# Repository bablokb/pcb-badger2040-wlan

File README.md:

pcb-badger2040-wlan
===================

A small pcb that allows to add an ESP-01S and/or PCF8523-RTC-breakout
to the back of a Pimoroni Badger2040 (or Tufty2040):

  - Badger2040 with SMD-pins:  

  - PCB added:  

  - ESP-01S connected:  

  - Additionally with RTC (PCF8523):  

Note that the images show an old Rev 3 version of the PCB.

Design-Files
------------

KiCAD source files are in `badger-2040-wlan.kicad`. Production files
for JLCPCB are in directory `production`. Since the pcb does not
need any SMD-components (in Rev 4), these pcb are really easy
to order (just upload the zip) and cheap (I got five for less
than 7 Euro).

Hack to wakeup the Badger2040 using the RTC
-------------------------------------------

If you don't use the ESP-01S, you can connect the
RTC-alarm pin to the INT-pin by closing the jumper on the
back. Note that wakeup will only work with battery if you
constantly hold one of the buttons pressed
(see <https://github.com/bablokb/badger2040-button-clamp>).

Also, wakup is currently not implemented in MicroPython.

License
-------

[![CC BY-SA 4.0][cc-by-sa-shield]][cc-by-sa]

This work is licensed under a
[Creative Commons Attribution-ShareAlike 4.0 International
License][cc-by-sa].

[![CC BY-SA 4.0][cc-by-sa-image]][cc-by-sa]

[cc-by-sa]: http://creativecommons.org/licenses/by-sa/4.0/
[cc-by-sa-image]: https://licensebuttons.net/l/by-sa/4.0/88x31.png
[cc-by-sa-shield]:
https://img.shields.io/badge/License-CC%20BY--SA%204.0-lightgrey.svg

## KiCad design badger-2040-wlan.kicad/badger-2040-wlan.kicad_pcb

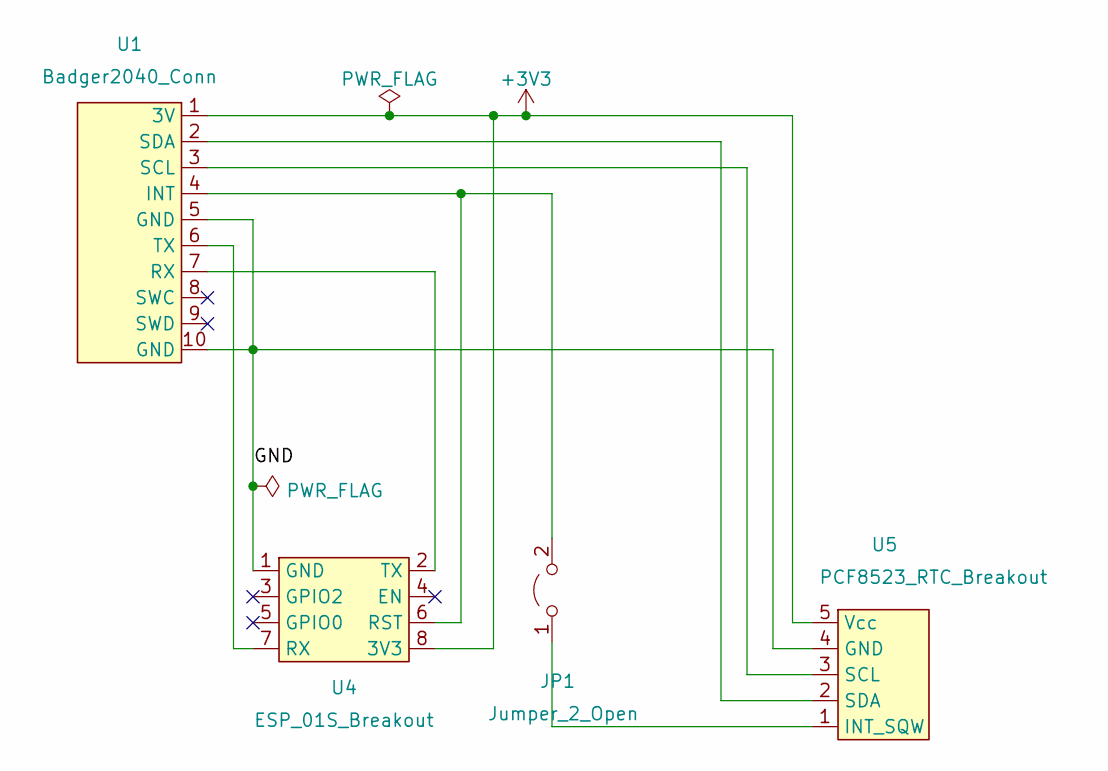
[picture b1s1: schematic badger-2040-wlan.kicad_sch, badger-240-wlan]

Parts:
JP1: Jumper_2_Open; SolderJumper-2_P1.3mm_Open_Pad1.0x1.5mm
U1: Badger2040_Conn; PinSocket_1x10_P2.54mm_Horizontal_Back
U4: ESP_01S_Breakout
U5: PCF8523_RTC_Breakout; PCF8523_Breakout

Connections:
+3V3: U1.1 (3V), U4.8 (3V3), U5.5 (Vcc)
/GND: U1.5 (GND), U1.10 (GND), U4.1 (GND), U5.4 (GND)
unnamed: JP1.1 (A), U5.1 (INT_SQW)
unnamed: JP1.2 (B), U1.4 (INT), U4.6 (RST)
unnamed: U1.2 (SDA), U5.2 (SDA)
unnamed: U1.3 (SCL), U5.3 (SCL)
unnamed: U1.6 (TX), U4.7 (RX)
unnamed: U1.7 (RX), U4.2 (TX)

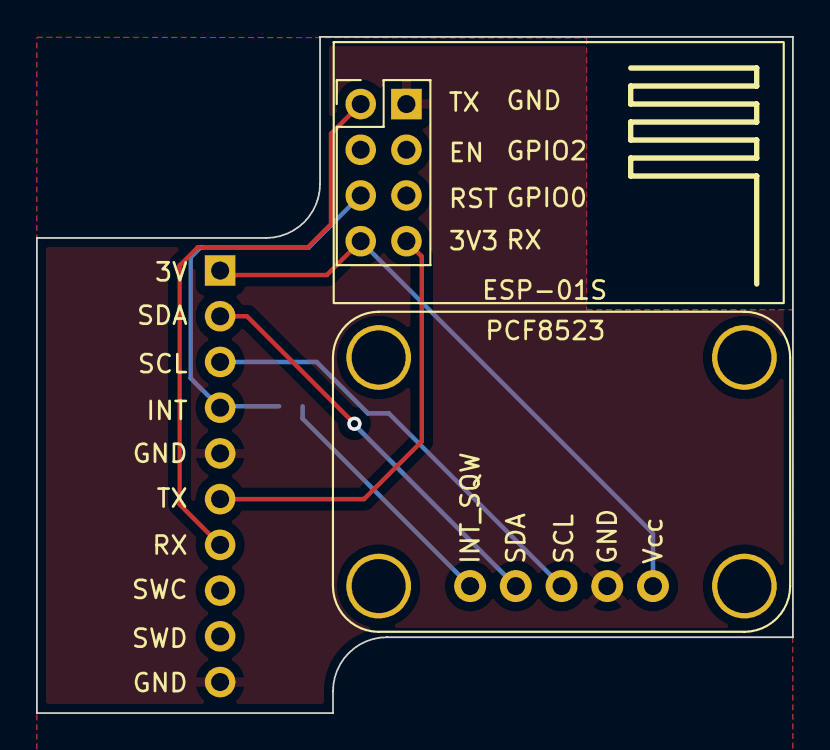
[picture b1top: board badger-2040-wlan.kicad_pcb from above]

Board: 2 copper layers, 42.0 x 37.6 mm, 4 parts (1 on the bottom side), 8 nets.

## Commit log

2022-10-22 intial commit
2022-10-22 added content
2022-11-12 Rev 4: removed pullup and inverter for RTC (INT_SQW)
2022-11-12 updated for Rev 4
2022-11-12 some additional notes
